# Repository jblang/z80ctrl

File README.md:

# z80ctrl

z80ctrl is an AVR-based bootloader, debugger, and I/O device for a Z80 retrocomputer with the following features:

- Plug-in module for [RC2014](https://rc2014.co.uk/) retrocomputer replaces the clock, serial, ROM, and CF boards
- Runs CP/M software directly from FAT32-formatted SD Card
- Boots unmodified disk images from the [AltairZ80](https://schorn.ch/altair.html) emulator
- Monitor with file management, memory inspector, and built-in Z80 disassembler
- Single-step debugging, breakpoints, and watchpoints to trace Z80 bus activity in real-time
- Expandable SPI bus allows bridging other SPI peripherals to the Z80
- Flexible MIT-licensed firmware can be the basis of your own SBC or breadboard computer

## Documentation

Much of the information that was previously here has been moved to separate wiki pages:

- [Board Assembly Instructions](https://github.com/jblang/z80ctrl/wiki/Board-Assembly-Instructions)
- [Monitor User Guide](https://github.com/jblang/z80ctrl/wiki/Monitor-User-Guide)
- [Known Issues](https://github.com/jblang/z80ctrl/wiki/Known-Issues)
- [Hardware Design Notes](https://github.com/jblang/z80ctrl/wiki/Hardware-Design-Notes)
- [Software Design Notes](https://github.com/jblang/z80ctrl/wiki/Software-Design-Notes)
- [IO Expander Board](https://github.com/jblang/z80ctrl/wiki/IO-Expander-Board)
- Check the [Wiki Index](https://github.com/jblang/z80ctrl/wiki) for other topics.

## Off-Site Resources

- [Hackaday Project Page](https://hackaday.io/project/158338-z80ctrl) with blog articles about various features.
- [YouTube Playlist](https://www.youtube.com/watch?v=M8EIAxMpA-o&list=PLwP_dSEH4Oi_jAljWQ1H-TBiBL34LqYYm)
- [RC2014 Google Group](https://groups.google.com/forum/#!forum/rc2014-z80). Search for z80ctrl to find previous discussion threads.
- [retro-comp Google Group](https://groups.google.com/g/retro-comp)

## License

Copyright 2018-2020 J.B. Langston

Permission is hereby granted, free of charge, to any person obtaining a copy of this software and associated documentation files (the "Software"), to deal in the Software without restriction, including without limitation the rights to use, copy, modify, merge, publish, distribute, sublicense, and/or sell copies of the Software, and to permit persons to whom the Software is furnished to do so, subject to the following conditions:

The above copyright notice and this permission notice shall be included in all copies or substantial portions of the Software.

THE SOFTWARE IS PROVIDED "AS IS", WITHOUT WARRANTY OF ANY KIND, EXPRESS OR IMPLIED, INCLUDING BUT NOT LIMITED TO THE WARRANTIES OF MERCHANTABILITY, FITNESS FOR A PARTICULAR PURPOSE AND NONINFRINGEMENT. IN NO EVENT SHALL THE AUTHORS OR COPYRIGHT HOLDERS BE LIABLE FOR ANY CLAIM, DAMAGES OR OTHER LIABILITY, WHETHER IN AN ACTION OF CONTRACT, TORT OR OTHERWISE, ARISING FROM, OUT OF OR IN CONNECTION WITH THE SOFTWARE OR THE USE OR OTHER DEALINGS IN THE SOFTWARE.

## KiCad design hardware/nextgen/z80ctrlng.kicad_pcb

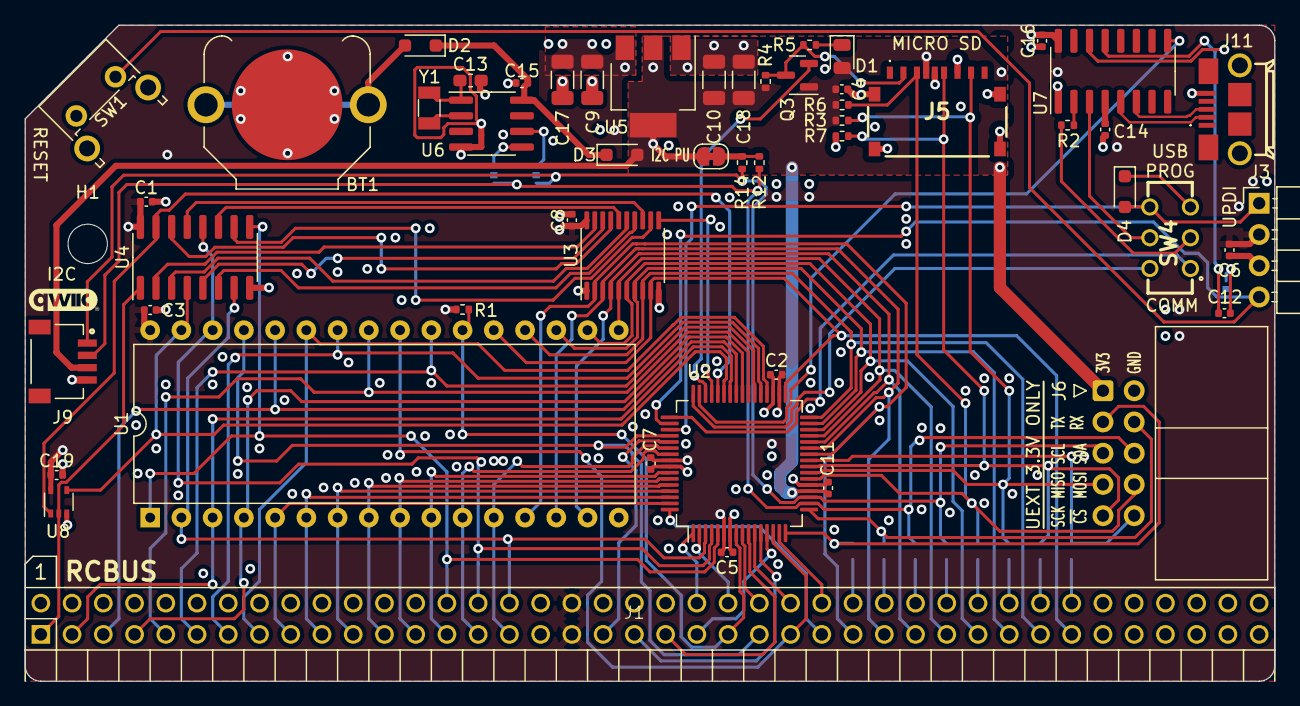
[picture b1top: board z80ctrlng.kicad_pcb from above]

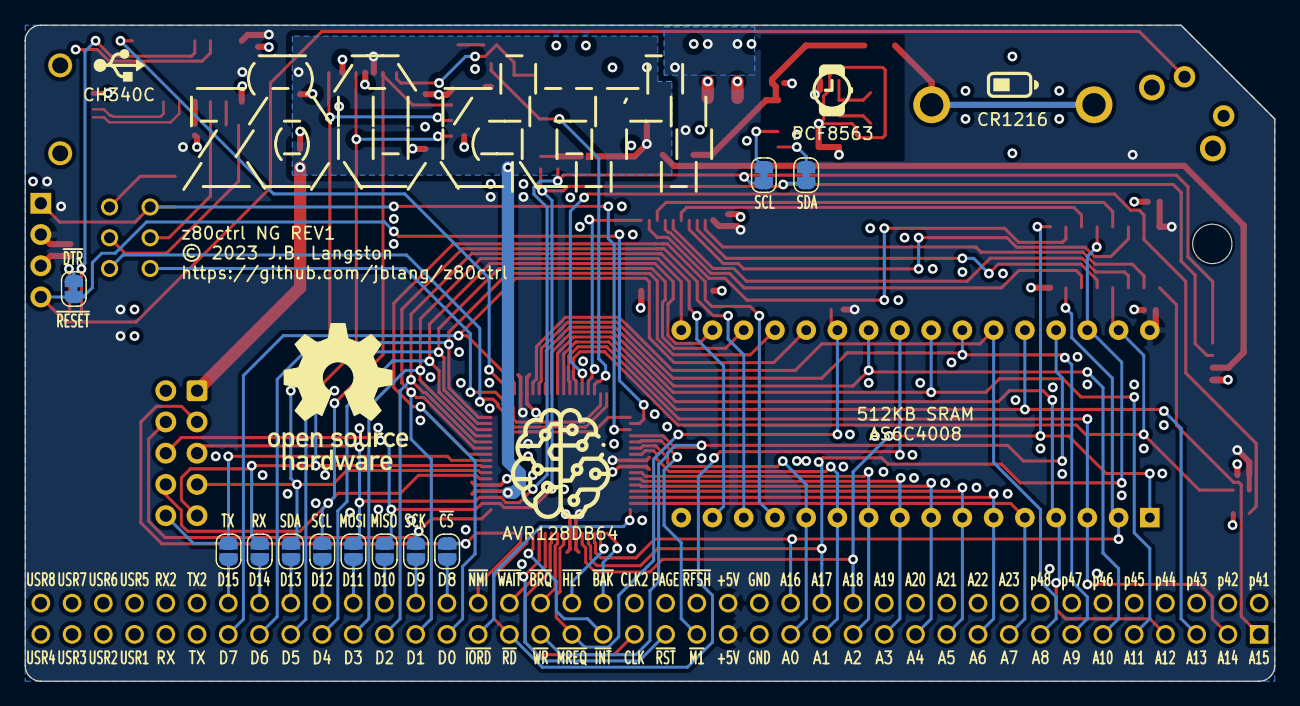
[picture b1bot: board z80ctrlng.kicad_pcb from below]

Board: 4 copper layers, 101.6 x 53.3 mm, 65 parts (11 on the bottom side), 95 nets.

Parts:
BT1: CR1216; BatteryHolder_Keystone_3001_1x12mm
C1, C2, C3, C4, C5, C6, C7, C8, C11, C12, C14, C15, C16, C19: 0.1uf; C_0402_1005Metric
C9, C10: 1uf; C_1206_3216Metric
C13: 27pf; C_0603_1608Metric_Pad1.08x0.95mm_HandSolder
C17, C18: 22uf; C_1206_3216Metric
D1: LED; LED_0805_2012Metric
D2, D3, D4: 1N5819WS; D_SOD-323_HandSoldering
H1: MountingHole; MountingHole_3.2mm_M3
J1: RCBUS; RCBus-80
J3: UDPI; PinHeader_1x04_P2.54mm_Horizontal
J5: XKTF-0803-0; XKTF08030
J6: UEXT; IDC-Header_2x05_P2.54mm_Horizontal
J9: SM04B-SRSS-TB; JST_SM04B-SRSS-TB_LF__SN_
J11: U254-051T-4BH81-S2S; U254051T4BH81S2S
JP1: AUTORESET; SolderJumper-2_P1.3mm_Bridged_RoundedPad1.0x1.5mm
JP2: TX3V; SolderJumper-2_P1.3mm_Open_RoundedPad1.0x1.5mm
JP3: RX3V; SolderJumper-2_P1.3mm_Open_RoundedPad1.0x1.5mm
JP6: SDA; SolderJumper-2_P1.3mm_Open_RoundedPad1.0x1.5mm
JP7: SCL; SolderJumper-2_P1.3mm_Open_RoundedPad1.0x1.5mm
JP8: MOSI; SolderJumper-2_P1.3mm_Open_RoundedPad1.0x1.5mm
JP9: MISO; SolderJumper-2_P1.3mm_Open_RoundedPad1.0x1.5mm
JP10: SCK; SolderJumper-2_P1.3mm_Open_RoundedPad1.0x1.5mm
JP11: CS; SolderJumper-2_P1.3mm_Open_RoundedPad1.0x1.5mm
JP13: RTC_SCL; SolderJumper-2_P1.3mm_Bridged_RoundedPad1.0x1.5mm
JP15: RTC_SDA; SolderJumper-2_P1.3mm_Bridged_RoundedPad1.0x1.5mm
JP16: I2C_PU; SolderJumper-2_P1.3mm_Bridged_RoundedPad1.0x1.5mm
NT1: NetTie_2; NetTie-2_SMD_Pad0.5mm
Q3: BSS138; SOT-23
R1: 10K; R_0402_1005Metric
R2, R5: 1K; R_0402_1005Metric
R3, R4, R6, R7: 100K; R_0402_1005Metric
R12, R14: 2.2K; R_0402_1005Metric
SW1: RESET; SW_Tactile_SPST_Angled_PTS645Vx31-2LFS
SW4: PROG_EN; JS202011CQN
U1: AS6C4008-55PCN; DIP-32_W15.24mm
U2: AVR128DB64x-xPT; TQFP-64_10x10mm_P0.5mm
U3: 74HCT573; TSSOP-20_4.4x6.5mm_P0.65mm
U4: 74HCT257; SOIC-16_3.9x9.9mm_P1.27mm
U5: AMS1117-3.3; SOT-223-3_TabPin2
U6: PCF8563T; SOIC-8_3.9x4.9mm_P1.27mm
U7: CH340C; SOIC-16_3.9x9.9mm_P1.27mm
U8: 74LVC1G126; SOT-353_SC-70-5
Y1: 32kHz; Crystal_SMD_3215-2Pin_3.2x1.5mm

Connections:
+3.3V: C4.1, C10.1, C11.1, C18.1, D1.2 (A), D3.2 (A), J5.P4 (VDD), J6.1, J9.3, JP16.2 (B), Q3.1 (G), R3.1, R4.1, R6.1, U2.20 (VDDIO2), U5.2 (VO)
+5V: C1.1, C2.1, C3.1, C5.1, C6.2, C7.1, C8.1, C9.1, C16.1, C17.1, C19.1, J1.18, J1.58, J3.2, R1.2, U1.32 (VCC), U2.6 (VDD), U2.34 (AVDD), U2.56 (VDD), U3.20 (VCC), U4.16 (VCC), U5.3 (VI), U7.16 (VCC), U8.5 (VCC)
/A0: J1.16, U1.12 (A0), U2.54 (PG2)
/A1: J1.15, U1.11 (A1), U2.55 (PG3)
/A2: J1.14, U1.10 (A2), U2.58 (PG4)
/A3: J1.13, U1.9 (A3), U2.59 (PG5)
/A4: J1.12, U1.8 (A4), U2.60 (PG6)
/A5: J1.11, U1.7 (A5), U2.61 (PG7)
/A6: J1.10, U1.6 (A6), U2.62 (XTALHF1/PA0)
/A7: J1.9, U1.5 (A7), U2.63 (XTALHF2/PA1)
/A8: J1.8, U1.27 (A8), U2.36 (PE0)
/A9: J1.7, U1.26 (A9), U2.37 (PE1)
/A10: J1.6, U1.23 (A10), U2.38 (PE2)
/A11: J1.5, U1.25 (A11), U2.39 (PE3)
/A12: J1.4, U1.4 (A12), U2.40 (PE4)
/A13: J1.3, U1.28 (A13), U2.41 (PE5)
/A14: J1.2, U1.3 (A14), U2.42 (PE6)
/A15: U1.31 (A15), U2.43 (PE7), U4.4 (Za), U8.4
/A15B: J1.1, U4.1 (S), U8.2
/A16: J1.56, U1.2 (A16), U2.3 (PA5), U4.7 (Zb)
/A17: J1.55, U1.30 (A17), U2.4 (PA6), U4.12 (Zc)
/A18: J1.54, U1.1 (A18), U2.5 (PA7), U4.9 (Zd)
/BA15: U3.19 (Q0), U4.2 (I0a)
/BA16: U3.18 (Q1), U4.5 (I0b)
/BA17: U3.17 (Q2), U4.14 (I0c)
/BA18: U3.16 (Q3), U4.11 (I0d)
/BB15: U3.15 (Q4), U4.3 (I1a)
/BB16: U3.14 (Q5), U4.6 (I1b)
/BB17: U3.13 (Q6), U4.13 (I1c)
/BB18: U3.12 (Q7), U4.10 (I1d)
/BLAT: U2.45 (XTAL32K2/PF1), U3.11 (Load)
/D0: J1.27, U1.13 (DQ0), U2.26 (PD0), U3.2 (D0)
/D1: J1.28, U1.14 (DQ1), U2.27 (PD1), U3.3 (D1)
/D2: J1.29, U1.15 (DQ2), U2.28 (PD2), U3.4 (D2)
/D3: J1.30, U1.17 (DQ3), U2.29 (PD3), U3.5 (D3)
/D4: J1.31, U1.18 (DQ4), U2.30 (PD4), U3.6 (D4)
/D5: J1.32, U1.19 (DQ5), U2.31 (PD5), U3.7 (D5)
/D6: J1.33, U1.20 (DQ6), U2.32 (PD6), U3.8 (D6)
/D7: J1.34, U1.21 (DQ7), U2.33 (VREFA/PD7), U3.9 (D7)
/D8: J1.67, JP2.1 (A)
/D9: J1.68, JP3.1 (A)
/D10: J1.69, JP6.2 (B)
/D11: J1.70, JP7.2 (B)
/D12: J1.71, JP8.2 (B)
/D13: J1.72, JP9.2 (B)
/D14: J1.73, JP10.2 (B)
/D15: J1.74, JP11.2 (B)
/Peripherals/UD+: J11.3 (D+), U7.6 (UD-)
/Peripherals/UD-: J11.2 (D-), U7.5 (UD+)
/Peripherals/USBRX: SW4.5 (B), U7.3 (RXD)
/Peripherals/USBTX: R2.2, SW4.2 (B)
/Z80CLK: J1.21, U2.10 (PB2)
/~BANK: U2.44 (XTAL32K1/PF0), U4.15 (OE), U8.1
/~BUSACK: J1.62, U2.1 (PA3)
/~BUSRQ: J1.64, U2.9 (PB1)
/~HALT: J1.63, U2.2 (PA4)
/~INT: J1.22, U2.13 (PB5)
/~IORQ: J1.26, U2.64 (PA2)
/~M1: J1.19, U2.53 (PG1)
/~MREQ: J1.23, R1.1, U1.22 (CE#), U2.8 (PB0)
/~NMI: J1.66, U2.15 (PB7)
/~RD: J1.25, U1.24 (OE#), U2.14 (PB6)
/~WAIT: J1.65, U2.11 (PB3)
/~WR: J1.24, U1.29 (WE#), U2.52 (PG0)
/~Z80RST: J1.20, U2.12 (PB4)
GND: BT1.2 (-), C1.2, C2.2, C3.2, C4.2, C5.2, C6.1, C7.2, C8.2, C9.2, C10.2, C11.2, C14.2, C15.2, C16.2, C17.2, C18.2, C19.2, J1.17, J1.57, J3.3, J5.G1 (DET), J5.MP1, J5.MP2, J5.MP3, J5.MP4, J5.P6 (VSS), J6.2, J9.4, J11.5 (GND), NT1.2, R7.1, SW1.1, U1.16 (VSS), U2.7 (GND), U2.21 (GND), U2.35 (AGND), U2.57 (GND), U3.1 (OE), U3.10 (GND), U4.8 (GND), U5.1 (GND), U6.4 (VSS), U7.1 (GND), U8.3 (GND)
GND1: C13.1, NT1.1
MISO: J5.P7 (DAT0), J6.7, JP9.1 (A), R3.2, U2.23 (PC5)
MOSI: J5.P3 (CMD), J6.8, JP8.1 (A), R6.2, U2.22 (PC4)
unnamed: BT1.1 (+), D2.2 (A)
unnamed: D1.1 (K), R5.2
unnamed: C15.1, D2.1 (K), D3.1 (K), U6.8 (VDD)
unnamed: D4.1 (K), SW4.3 (C)
unnamed: J5.P2 (DAT3/CD), Q3.3 (D), R4.2, R5.1
unnamed: C12.2, JP1.1 (A)
unnamed: JP13.2 (B), U6.6 (SCL)
unnamed: JP15.2 (B), U6.5 (SDA)
unnamed: JP16.1 (A), R12.1, R14.1
unnamed: C13.2, U6.1 (OSCI), Y1.2
unnamed: U6.2 (OSCO), Y1.1
unnamed: R2.1, U7.2 (TXD)
unnamed: C14.1, U7.4 (V3)
unnamed: C12.1, U7.13 (~DTR)
RXC: J6.4, JP3.2 (B), U2.17 (PC1)
RXF: SW4.1 (A), U2.49 (PF5)
SCK: J5.P5 (CLK), J6.9, JP10.1 (A), R7.2, U2.24 (PC6)
SCL: J6.5, J9.1, JP7.1 (A), JP13.1 (A), R14.2, U2.19 (PC3)
SDA: J6.6, J9.2, JP6.1 (A), JP15.1 (A), R12.2, U2.18 (PC2)
TXC: J6.3, JP2.2 (B), U2.16 (PC0)
TXF: SW4.4 (A), U2.48 (PF4)
UPDI: D4.2 (A), J3.1, SW4.6 (C), U2.51 (UPDI)
~CS: J6.10, JP11.1 (A), U2.25 (PC7)
~CTS: U2.47 (PF3), U7.9 (~CTS)
~RESET: J3.4, JP1.2 (B), SW1.2, U2.50 (~RESET/PF6)
~SDCS: Q3.2 (S), U2.46 (PF2)

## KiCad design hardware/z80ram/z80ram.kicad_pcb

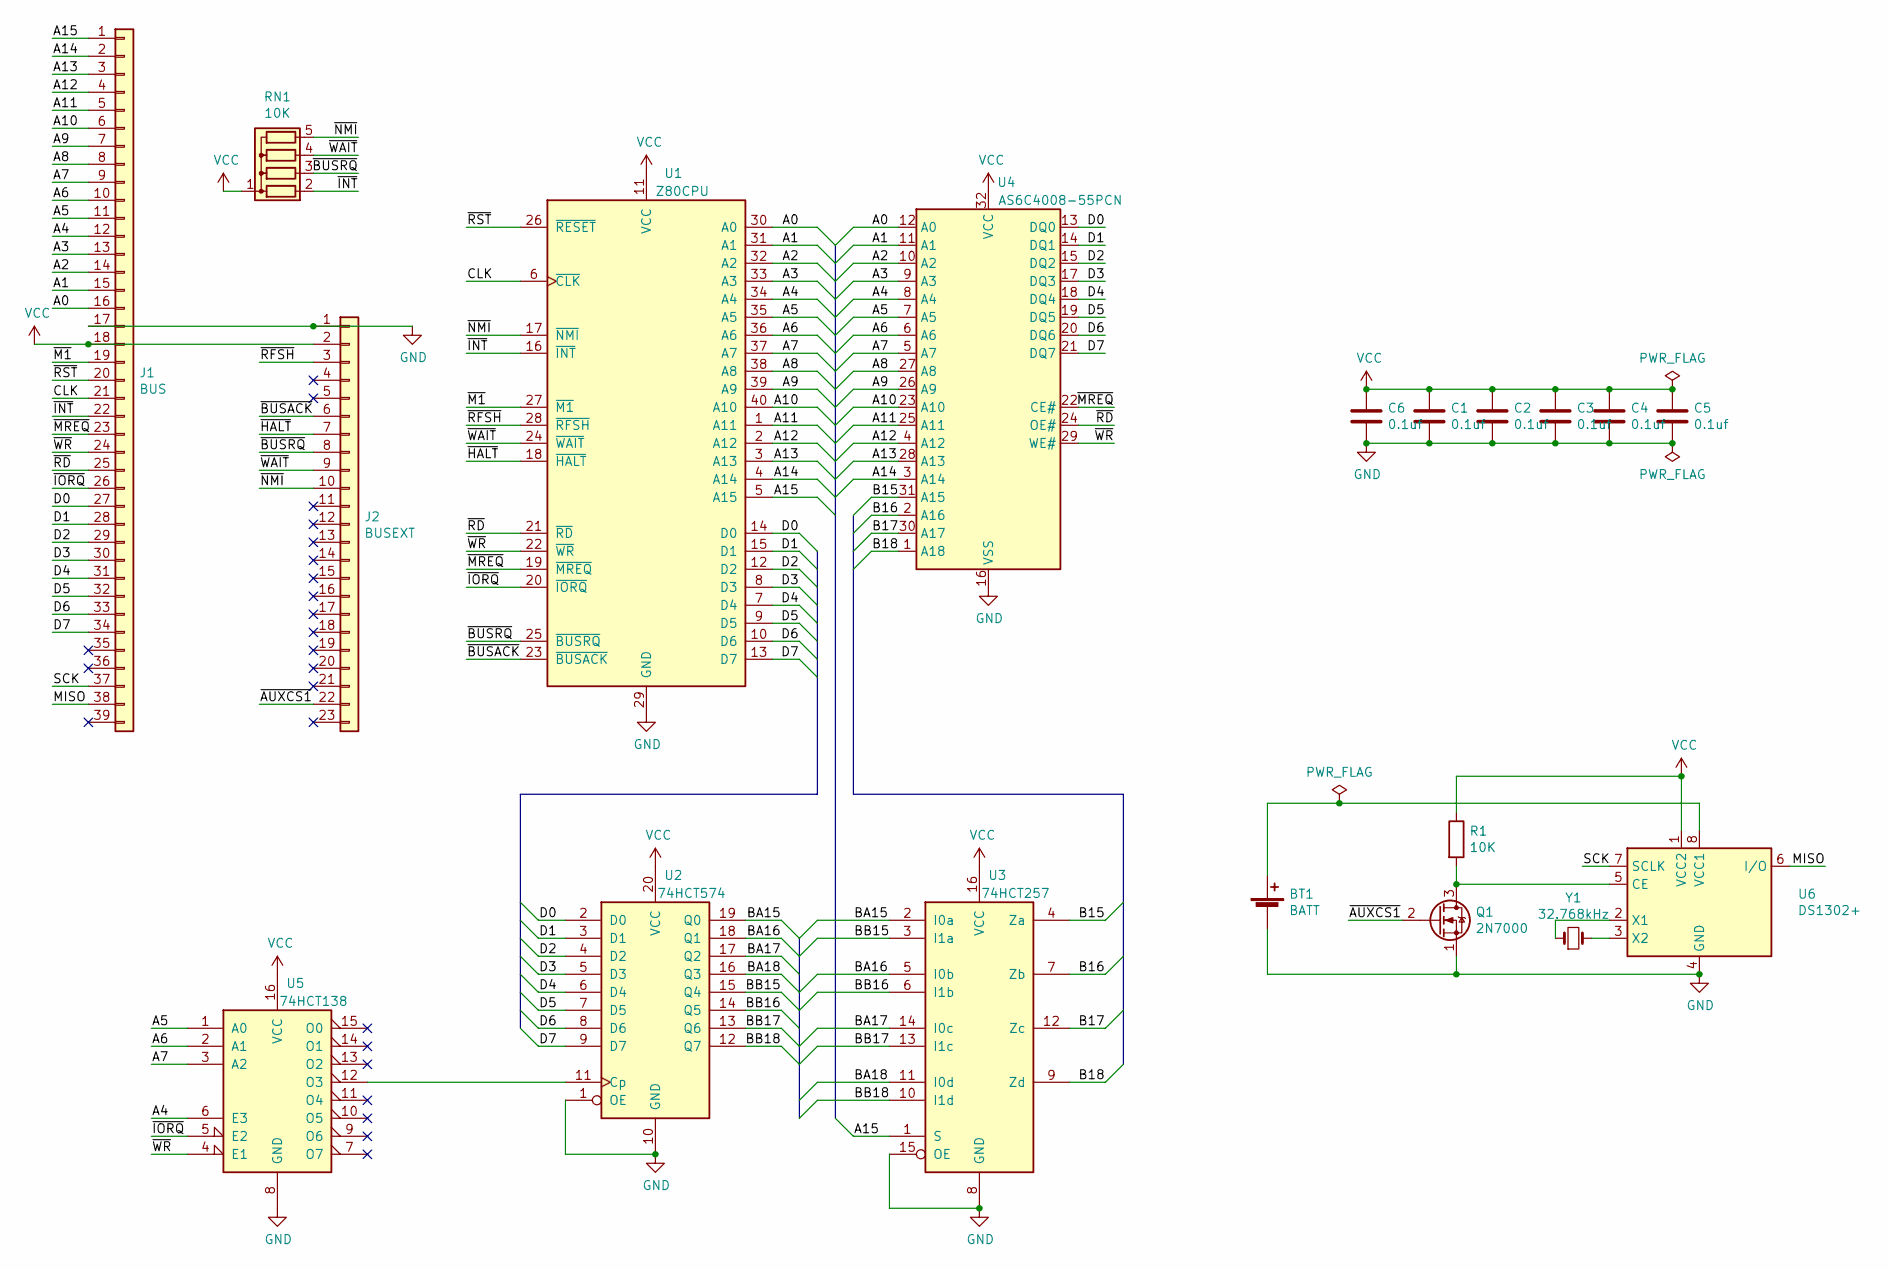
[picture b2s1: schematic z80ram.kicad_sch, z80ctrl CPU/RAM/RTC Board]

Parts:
BT1: BATT; BatteryHolder_Keystone_3001_1x12mm; MouserPN 534-3001; DigikeyPN 36-3001-ND
C1, C3, C4, C5, C6: 0.1uf; C_Disc_D3.0mm_W1.6mm_P2.50mm; MouserPN 594-K104M15X7RF53L2; DigikeyPN BC5142-ND
C2: 0.1uf; C_Disc_D3.0mm_W1.6mm_P2.50mm; DigikeyPN BC5142-ND
J1: BUS; PinHeader_1x39_P2.54mm_Vertical; MouserPN 517-5121TG; DigikeyPN 2057-PH2RA-80-UA-ND
J2: BUSEXT; PinHeader_1x23_P2.54mm_Vertical; MouserPN 517-5121TG; DigikeyPN 2057-PH2RA-80-UA-ND
Q1: 2N7000; TO-92_Inline; MouserPN 512-2N7000; DigikeyPN 2N7000FS-ND
R1: 10K; R_Axial_DIN0207_L6.3mm_D2.5mm_P7.62mm_Horizontal; MouserPN 603-CFR-25JB-52-10K; DigikeyPN 10KQBK-ND
RN1: 10K; R_Array_SIP5; MouserPN 652-4605M-1LF-10K; DigikeyPN 4605M-101-103LF-ND
U1: Z80CPU; DIP-40_W15.24mm; MouserPN 692-Z84C0010PEG; DigikeyPN 269-3898-ND
U2: 74HCT574; DIP-20_W7.62mm; MouserPN 595-SN74HCT574N; DigikeyPN 296-1623-5-ND
U3: 74HCT257; DIP-16_W7.62mm; MouserPN 595-SN74HCT257N; DigikeyPN 296-8406-5-ND
U4: AS6C4008-55PCN; DIP-32_W15.24mm; MouserPN 913-AS6C4008-55PCN; DigikeyPN 1450-1027-ND
U5: 74HCT138; DIP-16_W7.62mm; MouserPN 595-SN74HCT138N; DigikeyPN 296-1608-5-ND
U6: DS1302+; DIP-8_W7.62mm; MouserPN 700-DS1302; DigikeyPN DS1302+-ND
Y1: 32.768kHz; Crystal_DS26_D2.0mm_L6.0mm_Horizontal; MouserPN 695-CFS-20632768DZBB; DigikeyPN 300-8301-ND

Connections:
/A0: J1.16, U1.30 (A0), U4.12 (A0)
/A1: J1.15, U1.31 (A1), U4.11 (A1)
/A2: J1.14, U1.32 (A2), U4.10 (A2)
/A3: J1.13, U1.33 (A3), U4.9 (A3)
/A4: J1.12, U1.34 (A4), U4.8 (A4), U5.6 (E3)
/A5: J1.11, U1.35 (A5), U4.7 (A5), U5.1 (A0)
/A6: J1.10, U1.36 (A6), U4.6 (A6), U5.2 (A1)
/A7: J1.9, U1.37 (A7), U4.5 (A7), U5.3 (A2)
/A8: J1.8, U1.38 (A8), U4.27 (A8)
/A9: J1.7, U1.39 (A9), U4.26 (A9)
/A10: J1.6, U1.40 (A10), U4.23 (A10)
/A11: J1.5, U1.1 (A11), U4.25 (A11)
/A12: J1.4, U1.2 (A12), U4.4 (A12)
/A13: J1.3, U1.3 (A13), U4.28 (A13)
/A14: J1.2, U1.4 (A14), U4.3 (A14)
/A15: J1.1, U1.5 (A15), U3.1 (S)
/B15: U3.4 (Za), U4.31 (A15)
/B16: U3.7 (Zb), U4.2 (A16)
/B17: U3.12 (Zc), U4.30 (A17)
/B18: U3.9 (Zd), U4.1 (A18)
/BA15: U2.19 (Q0), U3.2 (I0a)
/BA16: U2.18 (Q1), U3.5 (I0b)
/BA17: U2.17 (Q2), U3.14 (I0c)
/BA18: U2.16 (Q3), U3.11 (I0d)
/BB15: U2.15 (Q4), U3.3 (I1a)
/BB16: U2.14 (Q5), U3.6 (I1b)
/BB17: U2.13 (Q6), U3.13 (I1c)
/BB18: U2.12 (Q7), U3.10 (I1d)
/CLK: J1.21, U1.6 (~CLK)
/D0: J1.27, U1.14 (D0), U2.2 (D0), U4.13 (DQ0)
/D1: J1.28, U1.15 (D1), U2.3 (D1), U4.14 (DQ1)
/D2: J1.29, U1.12 (D2), U2.4 (D2), U4.15 (DQ2)
/D3: J1.30, U1.8 (D3), U2.5 (D3), U4.17 (DQ3)
/D4: J1.31, U1.7 (D4), U2.6 (D4), U4.18 (DQ4)
/D5: J1.32, U1.9 (D5), U2.7 (D5), U4.19 (DQ5)
/D6: J1.33, U1.10 (D6), U2.8 (D6), U4.20 (DQ6)
/D7: J1.34, U1.13 (D7), U2.9 (D7), U4.21 (DQ7)
/MISO: J1.38, U6.6 (I/O)
/SCK: J1.37, U6.7 (SCLK)
/~AUXCS1: J2.22, Q1.2 (G)
/~BUSACK: J2.6, U1.23 (~BUSACK)
/~BUSRQ: J2.8, RN1.3 (R2), U1.25 (~BUSRQ)
/~HALT: J2.7, U1.18 (~HALT)
/~INT: J1.22, RN1.2 (R1), U1.16 (~INT)
/~IORQ: J1.26, U1.20 (~IORQ), U5.5 (E2)
/~M1: J1.19, U1.27 (~M1)
/~MREQ: J1.23, U1.19 (~MREQ), U4.22 (CE#)
/~NMI: J2.10, RN1.5 (R4), U1.17 (~NMI)
/~RD: J1.25, U1.21 (~RD), U4.24 (OE#)
/~RFSH: J2.3, U1.28 (~RFSH)
/~RST: J1.20, U1.26 (~RESET)
/~WAIT: J2.9, RN1.4 (R3), U1.24 (~WAIT)
/~WR: J1.24, U1.22 (~WR), U4.29 (WE#), U5.4 (E1)
GND: BT1.2 (-), C1.2, C2.2, C3.2, C4.2, C5.2, C6.2, J1.17, J2.1, Q1.1 (S), U1.29 (GND), U2.1 (OE), U2.10 (GND), U3.8 (GND), U3.15 (OE), U4.16 (VSS), U5.8 (GND), U6.4 (GND)
unnamed: BT1.1 (+), U6.8 (VCC1)
unnamed: Q1.3 (D), R1.2, U6.5 (CE)
unnamed: U2.11 (Cp), U5.12 (O3)
unnamed: U6.2 (X1), Y1.1
unnamed: U6.3 (X2), Y1.2
VCC: C1.1, C2.1, C3.1, C4.1, C5.1, C6.1, J1.18, J2.2, R1.1, RN1.1 (common), U1.11 (VCC), U2.20 (VCC), U3.16 (VCC), U4.32 (VCC), U5.16 (VCC), U6.1 (VCC2)

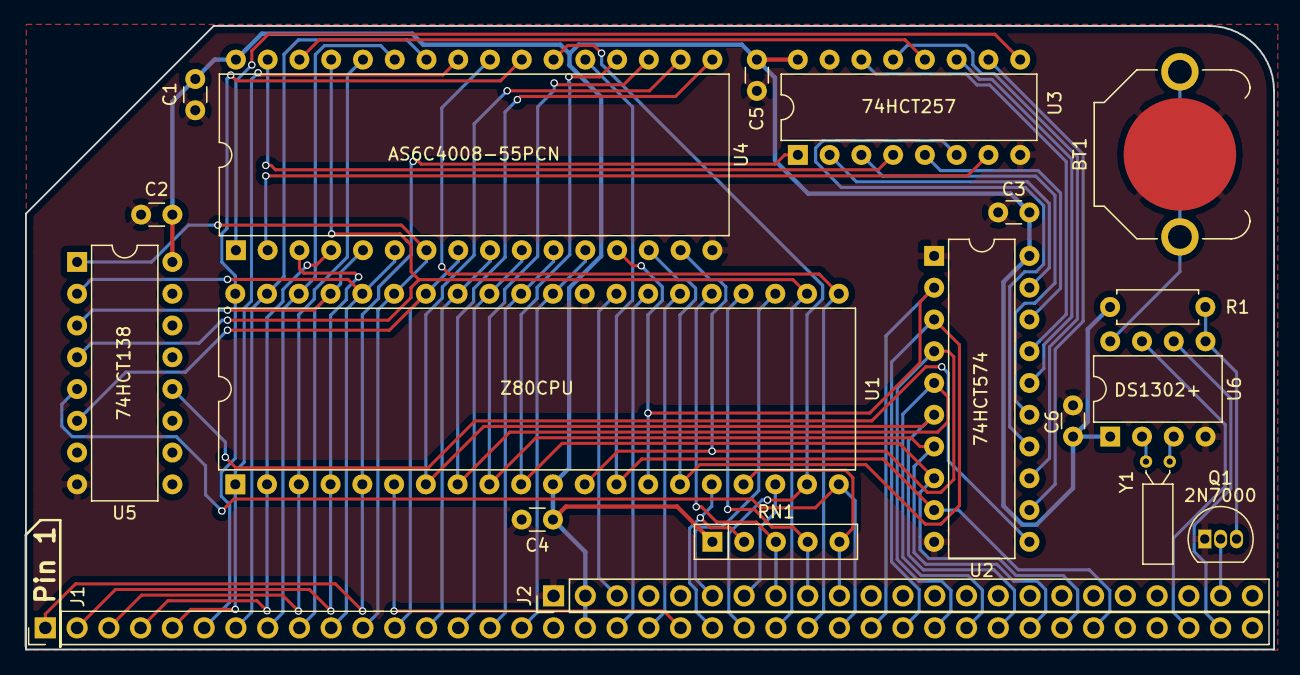
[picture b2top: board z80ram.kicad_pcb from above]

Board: 2 copper layers, 99.8 x 49.9 mm, 19 parts (0 on the bottom side), 60 nets.

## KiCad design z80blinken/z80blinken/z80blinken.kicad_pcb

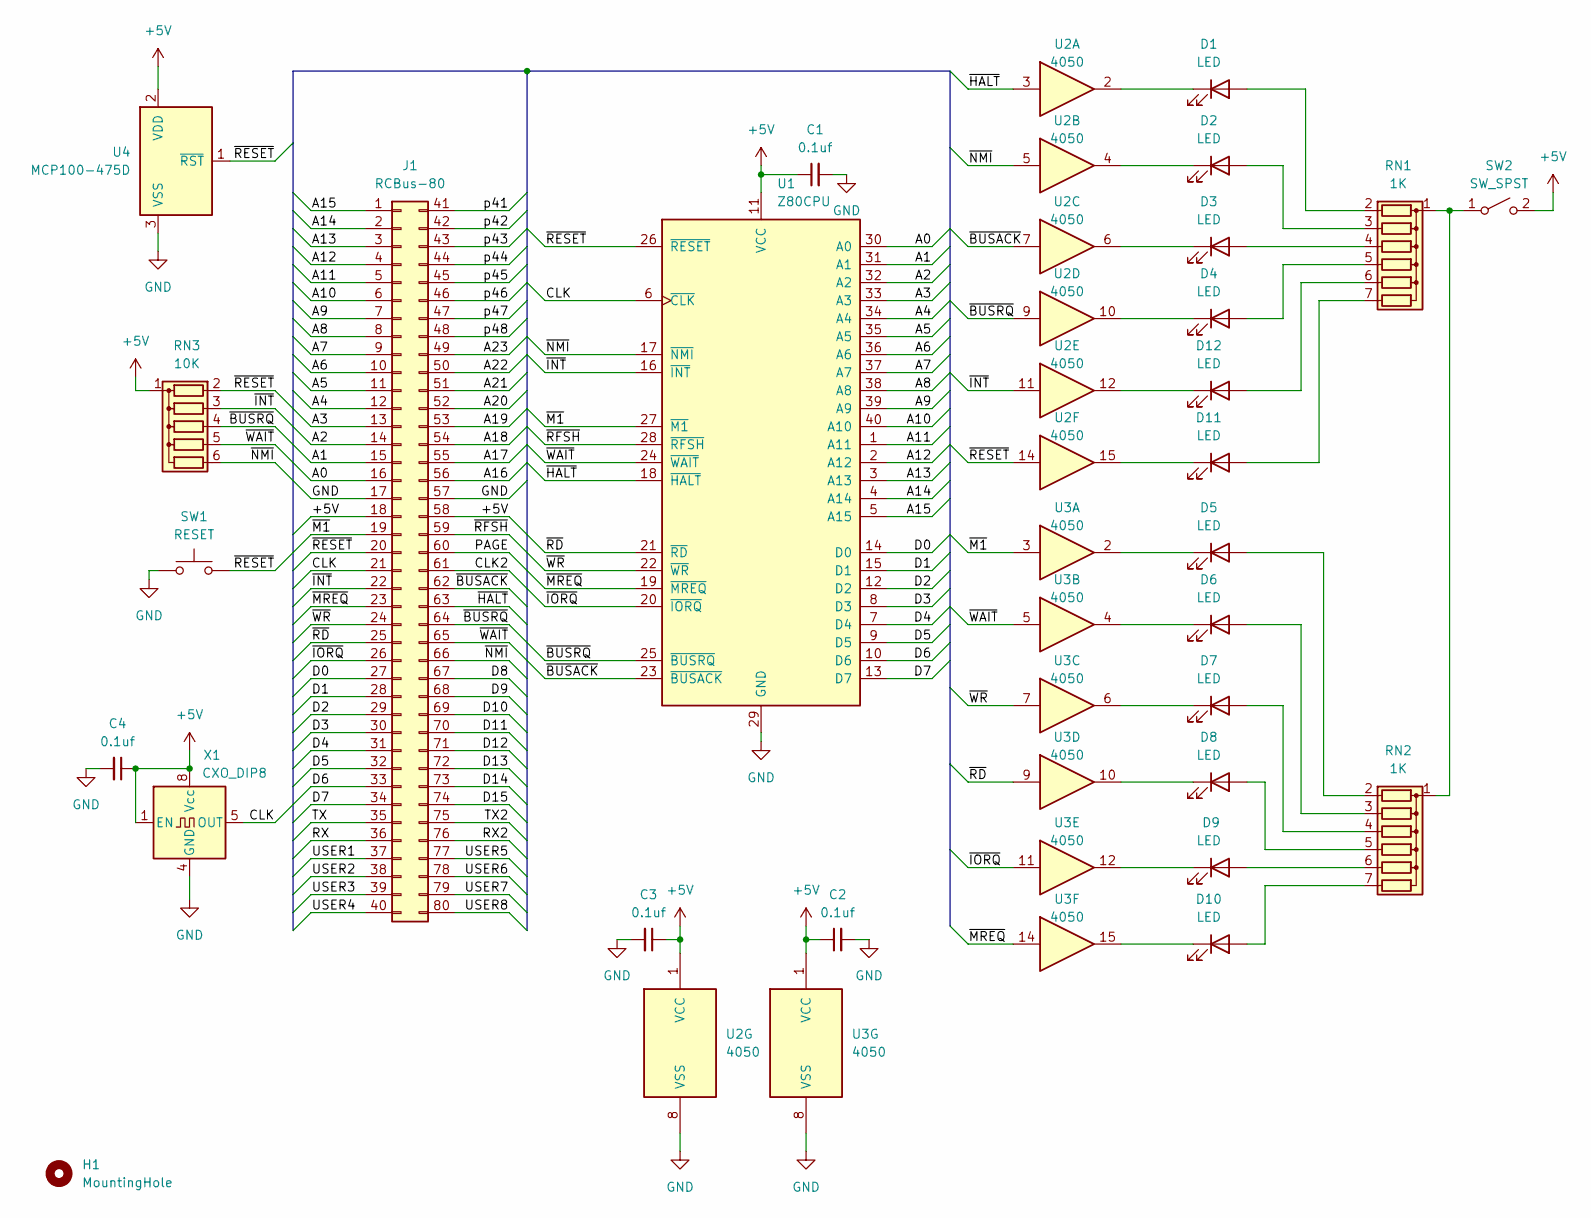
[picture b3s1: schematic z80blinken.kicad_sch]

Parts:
C1, C2, C3, C4: 0.1uf; C_Disc_D3.0mm_W1.6mm_P2.50mm
D1, D2, D3, D4, D5, D6, D7, D8, D9, D10, D11, D12: LED; LED_WP934CB&slash_GD_KNB
H1: MountingHole; MountingHole_3.2mm_M3
J1: RCBus-80
RN1, RN2: 1K; R_Array_SIP7
RN3: 10K; R_Array_SIP6
SW1: RESET; SW_Tactile_SPST_Angled_PTS645Vx31-2LFS
SW2: SW_SPST; JS202011CQN
U1: Z80CPU; DIP-40_W15.24mm
U2, U3: 4050; DIP-16_W7.62mm
U4: MCP100-475D; TO-92_Inline
X1: CXO_DIP8; Oscillator_DIP-8

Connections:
+5V: C1.1, C2.1, C3.1, C4.1, J1.18, J1.58, RN3.1 (common), SW2.2 (B), U1.11 (VCC), U2.1 (VCC), U3.1 (VCC), U4.2 (VDD), X1.1 (EN), X1.8 (Vcc)
/A0: J1.16, U1.30 (A0)
/A1: J1.15, U1.31 (A1)
/A2: J1.14, U1.32 (A2)
/A3: J1.13, U1.33 (A3)
/A4: J1.12, U1.34 (A4)
/A5: J1.11, U1.35 (A5)
/A6: J1.10, U1.36 (A6)
/A7: J1.9, U1.37 (A7)
/A8: J1.8, U1.38 (A8)
/A9: J1.7, U1.39 (A9)
/A10: J1.6, U1.40 (A10)
/A11: J1.5, U1.1 (A11)
/A12: J1.4, U1.2 (A12)
/A13: J1.3, U1.3 (A13)
/A14: J1.2, U1.4 (A14)
/A15: J1.1, U1.5 (A15)
/A16: J1.56
/A17: J1.55
/A18: J1.54
/A19: J1.53
/A20: J1.52
/A21: J1.51
/A22: J1.50
/A23: J1.49
/CLK: J1.21, U1.6 (~CLK), X1.5 (OUT)
/CLK2: J1.61
/D0: J1.27, U1.14 (D0)
/D1: J1.28, U1.15 (D1)
/D2: J1.29, U1.12 (D2)
/D3: J1.30, U1.8 (D3)
/D4: J1.31, U1.7 (D4)
/D5: J1.32, U1.9 (D5)
/D6: J1.33, U1.10 (D6)
/D7: J1.34, U1.13 (D7)
/D8: J1.67
/D9: J1.68
/D10: J1.69
/D11: J1.70
/D12: J1.71
/D13: J1.72
/D14: J1.73
/D15: J1.74
/PAGE: J1.60
/RX: J1.36
/RX2: J1.76
/TX: J1.35
/TX2: J1.75
/USER1: J1.37
/USER2: J1.38
/USER3: J1.39
/USER4: J1.40
/USER5: J1.77
/USER6: J1.78
/USER7: J1.79
/USER8: J1.80
/p41: J1.41
/p42: J1.42
/p43: J1.43
/p44: J1.44
/p45: J1.45
/p46: J1.46
/p47: J1.47
/p48: J1.48
/~BUSACK: J1.62, U1.23 (~BUSACK), U2.7
/~BUSRQ: J1.64, RN3.4 (R3), U1.25 (~BUSRQ), U2.9
/~HALT: J1.63, U1.18 (~HALT), U2.3
/~INT: J1.22, RN3.3 (R2), U1.16 (~INT), U2.11
/~IORQ: J1.26, U1.20 (~IORQ), U3.11
/~M1: J1.19, U1.27 (~M1), U3.3
/~MREQ: J1.23, U1.19 (~MREQ), U3.14
/~NMI: J1.66, RN3.6 (R5), U1.17 (~NMI), U2.5
/~RD: J1.25, U1.21 (~RD), U3.9
/~RESET: J1.20, RN3.2 (R1), SW1.2, U1.26 (~RESET), U2.14, U4.1 (~RST)
/~RFSH: J1.59, U1.28 (~RFSH)
/~WAIT: J1.65, RN3.5 (R4), U1.24 (~WAIT), U3.5
/~WR: J1.24, U1.22 (~WR), U3.7
GND: C1.2, C2.2, C3.2, C4.2, J1.17, J1.57, SW1.1, U1.29 (GND), U2.8 (VSS), U3.8 (VSS), U4.3 (VSS), X1.4 (GND)
unnamed: D1.2 (A), RN1.2 (R1)
unnamed: D1.1 (K), U2.2
unnamed: D2.2 (A), RN1.3 (R2)
unnamed: D2.1 (K), U2.4
unnamed: D3.2 (A), RN1.4 (R3)
unnamed: D3.1 (K), U2.6
unnamed: D4.2 (A), RN1.5 (R4)
unnamed: D4.1 (K), U2.10
unnamed: D5.2 (A), RN2.2 (R1)
unnamed: D5.1 (K), U3.2
unnamed: D6.2 (A), RN2.3 (R2)
unnamed: D6.1 (K), U3.4
unnamed: D7.2 (A), RN2.4 (R3)
unnamed: D7.1 (K), U3.6
unnamed: D8.2 (A), RN2.5 (R4)
unnamed: D8.1 (K), U3.10
unnamed: D9.2 (A), RN2.6 (R5)
unnamed: D9.1 (K), U3.12
unnamed: D10.2 (A), RN2.7 (R6)
unnamed: D10.1 (K), U3.15
unnamed: D11.2 (A), RN1.7 (R6)
unnamed: D11.1 (K), U2.15
unnamed: D12.2 (A), RN1.6 (R5)
unnamed: D12.1 (K), U2.12
unnamed: RN1.1 (common), RN2.1 (common), SW2.1 (A)

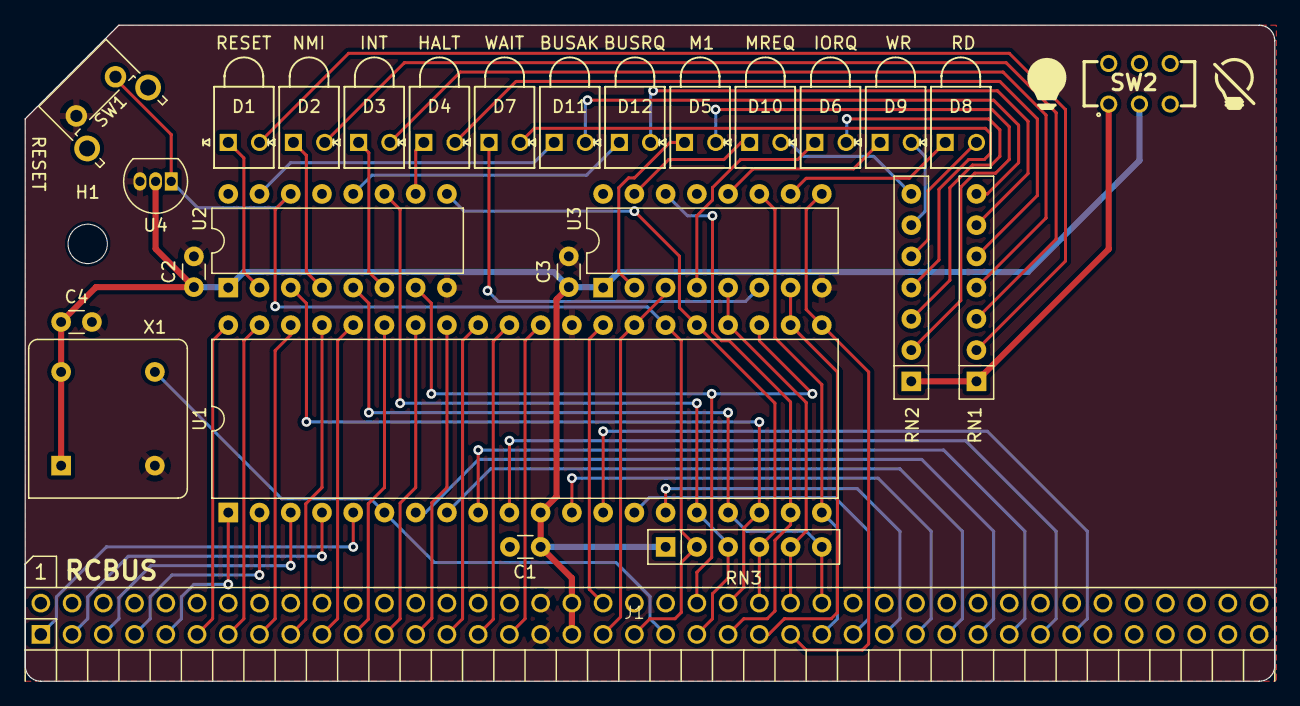
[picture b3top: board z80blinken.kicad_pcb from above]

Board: 2 copper layers, 101.6 x 53.3 mm, 28 parts (0 on the bottom side), 65 nets.

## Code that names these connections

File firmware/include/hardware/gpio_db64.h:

/* z80ctrl (https://github.com/jblang/z80ctrl)
 * Copyright 2018-2023 J.B. Langston
 *
 * Permission is hereby granted, free of charge, to any person obtaining a
 * copy of this software and associated documentation files (the "Software"),
 * to deal in the Software without restriction, including without limitation
 * the rights to use, copy, modify, merge, publish, distribute, sublicense,
 * and/or sell copies of the Software, and to permit persons to whom the
 * Software is furnished to do so, subject to the following conditions:
 *
 * The above copyright notice and this permission notice shall be included in
 * all copies or substantial portions of the Software.
 *
 * THE SOFTWARE IS PROVIDED "AS IS", WITHOUT WARRANTY OF ANY KIND, EXPRESS OR
 * IMPLIED, INCLUDING BUT NOT LIMITED TO THE WARRANTIES OF MERCHANTABILITY,
 * FITNESS FOR A PARTICULAR PURPOSE AND NONINFRINGEMENT. IN NO EVENT SHALL THE
 * AUTHORS OR COPYRIGHT HOLDERS BE LIABLE FOR ANY CLAIM, DAMAGES OR OTHER
 * LIABILITY, WHETHER IN AN ACTION OF CONTRACT, TORT OR OTHERWISE, ARISING
 * FROM, OUT OF OR IN CONNECTION WITH THE SOFTWARE OR THE USE OR OTHER
 * DEALINGS IN THE SOFTWARE.
 */

/**
 * @file gipo_db64.h GPIO pin assignments for AVR128DB64
 */

#ifndef HARDWARE_GPIO_DB64_H
#define HARDWARE_GPIO_DB64_H

#include <avr/io.h>

#include "mcp23s17.h"

/**
 * Address Bus
 */

#define ADDRLO_DDR DDRA
#define ADDRLO_PORT PORTA
#define ADDRLO_PIN PINA

#if (BOARD_REV == 3 || BOARD_REV == 4)
#define ADDRHI_IODIR IODIRA
#define ADDRHI_GPPU GPPUA
#define ADDRHI_GPIO GPIOA
#elif (BOARD_REV == 5 || BOARD_REV == 6)
#define ADDRHI_IODIR IODIRB
#define ADDRHI_GPPU GPPUB
#define ADDRHI_GPIO GPIOB
#else
#error "Unsupported board revision. Set BOARD_REV in your Makefile to match your board revision."
#endif

#define ADDR_INPUT (ADDRLO_DDR = 0x00, iox0_write(ADDRHI_IODIR, 0xFF))
#define ADDR_OUTPUT (ADDRLO_DDR = 0xFF, iox0_write(ADDRHI_IODIR, 0x00))

#define GET_ADDRLO ADDRLO_PIN
#define SET_ADDRLO(addr) ADDRLO_PORT = (addr)

#define GET_ADDRHI iox0_read(ADDRHI_GPIO)
#define SET_ADDRHI(addr) iox0_write(ADDRHI_GPIO, (addr))

#define GET_ADDR (GET_ADDRLO | (GET_ADDRHI << 8))
#define SET_ADDR(addr) (SET_ADDRLO((addr) & 0xFF), SET_ADDRHI((addr) >> 8))

/**
 * Data Bus
 */

#define DATA_DDR DDRC
#define DATA_PORT PORTC
#define DATA_PIN PINC

#define DATA_INPUT DATA_DDR = 0x00
#define DATA_OUTPUT DATA_DDR = 0xFF
#define GET_DATA DATA_PIN
#define SET_DATA(data) DATA_PORT = (data)

/**
 * PORTB flags
 */

#define BUSRQ (1 << 0)

#define GET_BUSRQ (PINB & BUSRQ)
#define BUSRQ_STATUS (status.flags & BUSRQ)
#define BUSRQ_HI PORTB |= BUSRQ
#define BUSRQ_LO PORTB &= ~BUSRQ

#define CTRLB_MASK 0x0F
#define CTRLB_OUTPUT_INIT DDRB |= BUSRQ

#if (BOARD_REV == 3 || BOARD_REV == 4)
#define IORQ (1 << 1)
#define MREQ (1 << 2)

#define GET_MREQ (PINB & MREQ)
#define MREQ_STATUS (status.flags & MREQ)
#define MREQ_HI PORTB |= MREQ
#define MREQ_LO PORTB &= ~MREQ

#define GET_IORQ (PINB & IORQ)
#define IORQ_STATUS (status.flags & IORQ)
#define IORQ_HI PORTB |= IORQ
#define IORQ_LO PORTB &= ~IORQ

#define IOMR_HI PORTB |= (IORQ | MREQ)
#define IOMR_OUTPUT DDRB |= (IORQ | MREQ)
#define IOMR_INPUT DDRB &= ~(IORQ | MREQ)

#define GET_WAIT (GET_IORQ || !GET_BUSRQ)
#define WAIT_STATUS (IORQ_STATUS || !BUSRQ_STATUS)

#define GET_IOXINT 0
#define IOXINT_STATUS 0
#elif (BOARD_REV == 5 || BOARD_REV == 6)
#define WAIT (1 << 1)
#define IOXINT (1 << 2)

#define GET_WAIT (PINB & WAIT)
#define WAIT_STATUS (status.flags & WAIT)

#define GET_IOXINT (PINB & IOXINT)
#define IOXINT_STATUS (status.flags & IOXINT)
#endif

/**
 * PORTD Flags
 */

#define RD (1 << 4)
#define WR (1 << 5)
#define CLK (1 << 6)
#define BUSACK (1 << 7)

#define GET_RD (PIND & RD)
#define RD_STATUS (status.flags & RD)
#define RD_HI PORTD |= RD
#define RD_LO PORTD &= ~RD

#define GET_WR (PIND & WR)
#define WR_STATUS (status.flags & WR)
#define WR_HI PORTD |= WR
#define WR_LO PORTD &= ~WR

#define RDWR_INPUT DDRD &= ~(RD | WR)
#define RDWR_OUTPUT DDRD |= (RD | WR)
#define RDWR_HI PORTD |= (RD | WR)

#define GET_CLK (PIND & CLK)
#define CLK_STATUS (status.flags & CLK)
#define CLK_HI PORTD |= CLK
#define CLK_LO PORTD &= ~CLK
#define CLK_TOGGLE PIND |= CLK

#define GET_BUSACK (PIND & BUSACK)
#define BUSACK_STATUS (status.flags & BUSACK)

#define CTRLD_MASK 0xF0
#define CTRLD_OUTPUT_INIT DDRD |= CLK

/**
 * IOX flags
 */

#if (BOARD_REV == 3 || BOARD_REV == 4)
#define CTRLX_IODIR IODIRB
#define CTRLX_GPPU GPPUB
#define CTRLX_GPIO GPIOB
#define CTRLX_INTCON INTCONB
#define CTRLX_DEFVAL DEFVALB
#define CTRLX_GPINTEN GPINTENB
#define CTRLX_INTCAP INTCAPB
#define RFSH (1 << 1)
#define RESET (1 << 2)
#define INTERRUPT (1 << 3)
#define M1 (1 << 4)
#define HALT (1 << 5)
#define NMI (1 << 7)

#define CTRLX_OUTPUT_INIT // No-op

#define GET_RFSH (iox0_read(CTRLX_GPIO) & RFSH)
#define RFSH_STATUS (status.xflags & RFSH)

#elif (BOARD_REV == 5 || BOARD_REV == 6)
#define CTRLX_IODIR IODIRA
#define CTRLX_GPPU GPPUA
#define CTRLX_GPIO GPIOA
#define CTRLX_INTCON INTCONA
#define CTRLX_DEFVAL DEFVALA
#define CTRLX_GPINTEN GPINTENA
#define CTRLX_INTCAP INTCAPA
#define M1 (1 << 0)
#define RESET (1 << 1)
#define INTERRUPT (1 << 2)
#define IORQ (1 << 3)
#define NMI (1 << 4)
#define HALT (1 << 5)
#define MREQ (1 << 6)
#define MWAIT (1 << 7)

#define CTRLX_OUTPUT_INIT iox0_clear(CTRLX_IODIR, MWAIT)

#define GET_MWAIT (iox0_read(CTRLX_GPIO) & MWAIT)
#define MWAIT_STATUS (status.xflags & MWAIT)
#define MWAIT_LO iox0_clear(CTRLX_GPIO, MWAIT)
#define MWAIT_HI iox0_set(CTRLX_GPIO, MWAIT)

#define GET_MREQ (iox0_read(CTRLX_GPIO) & MREQ)
#define MREQ_STATUS (status.xflags & MREQ)
#define MREQ_LO iox0_clear(CTRLX_GPIO, MREQ)
#define MREQ_HI iox0_set(CTRLX_GPIO, MREQ)

#define GET_IORQ (iox0_read(CTRLX_GPIO) & IORQ)
#define IORQ_STATUS (status.xflags & IORQ)
#define IORQ_LO iox0_clear(CTRLX_GPIO, IORQ)
#define IORQ_HI iox0_set(CTRLX_GPIO, IORQ)

#define IOMR_INPUT iox0_set(CTRLX_IODIR, IORQ | MREQ)
#define IOMR_OUTPUT iox0_clear(CTRLX_IODIR, IORQ | MREQ)
#define IOMR_HI iox0_set(CTRLX_GPIO, IORQ | MREQ)

#define GET_RFSH (GET_MREQ || !(GET_RD && GET_WR))
#define RFSH_STATUS (MREQ_STATUS || !(RD_STATUS && WR_STATUS))
#endif

#define GET_M1 (iox0_read(CTRLX_GPIO) & M1)
#define M1_STATUS (status.xflags & M1)

#define GET_HALT (iox0_read(CTRLX_GPIO) & HALT)
#define HALT_STATUS (status.xflags & HALT)

// RESET, INT, and NMI behave like an open drain. It is only an output when it is low.
#define GET_RESET (iox0_read(CTRLX_GPIO) & RESET)
#define RESET_STATUS (status.xflags & RESET)
#define RESET_OUTPUT iox0_clear(CTRLX_IODIR, RESET)
#define RESET_INPUT iox0_set(CTRLX_IODIR, RESET)

#define GET_INT (iox0_read(CTRLX_GPIO) & INTERRUPT)
#define INT_STATUS (status.xflags & INTERRUPT)
#define INT_OUTPUT iox0_clear(CTRLX_IODIR, INTERRUPT)
#define INT_INPUT iox0_set(CTRLX_IODIR, INTERRUPT)

#define GET_NMI (iox0_read(CTRLX_GPIO) & NMI)
#define NMI_STATUS (status.xflags & NMI)
#define NMI_OUTPUT iox0_clear(CTRLX_IODIR, NMI)
#define NMI_INPUT iox0_set(CTRLX_IODIR, NMI)

#define CTRLX_PULLUP_INIT iox0_set(CTRLX_GPPU, (HALT | RESET | INTERRUPT | NMI))

#endif

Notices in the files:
avr128db64/avr128db64.kicad_pcb:
(C)2023 J.B. Langston
hardware/nextgen/z80ctrlng.kicad_pcb:
© 2023 J.B. Langston
hardware/z80blinken/z80blinken.kicad_sch:
(C) 2024 J.B. Langston
hardware/z80ctrl.kicad_pcb:
(C)2020 J.B. Langston
iox/z80ctrl-iox.kicad_pcb:
(C)2018 J.B. Langston
z80blinken/z80blinken/z80blinken.kicad_pcb:
© 2024 J.B. Langston
